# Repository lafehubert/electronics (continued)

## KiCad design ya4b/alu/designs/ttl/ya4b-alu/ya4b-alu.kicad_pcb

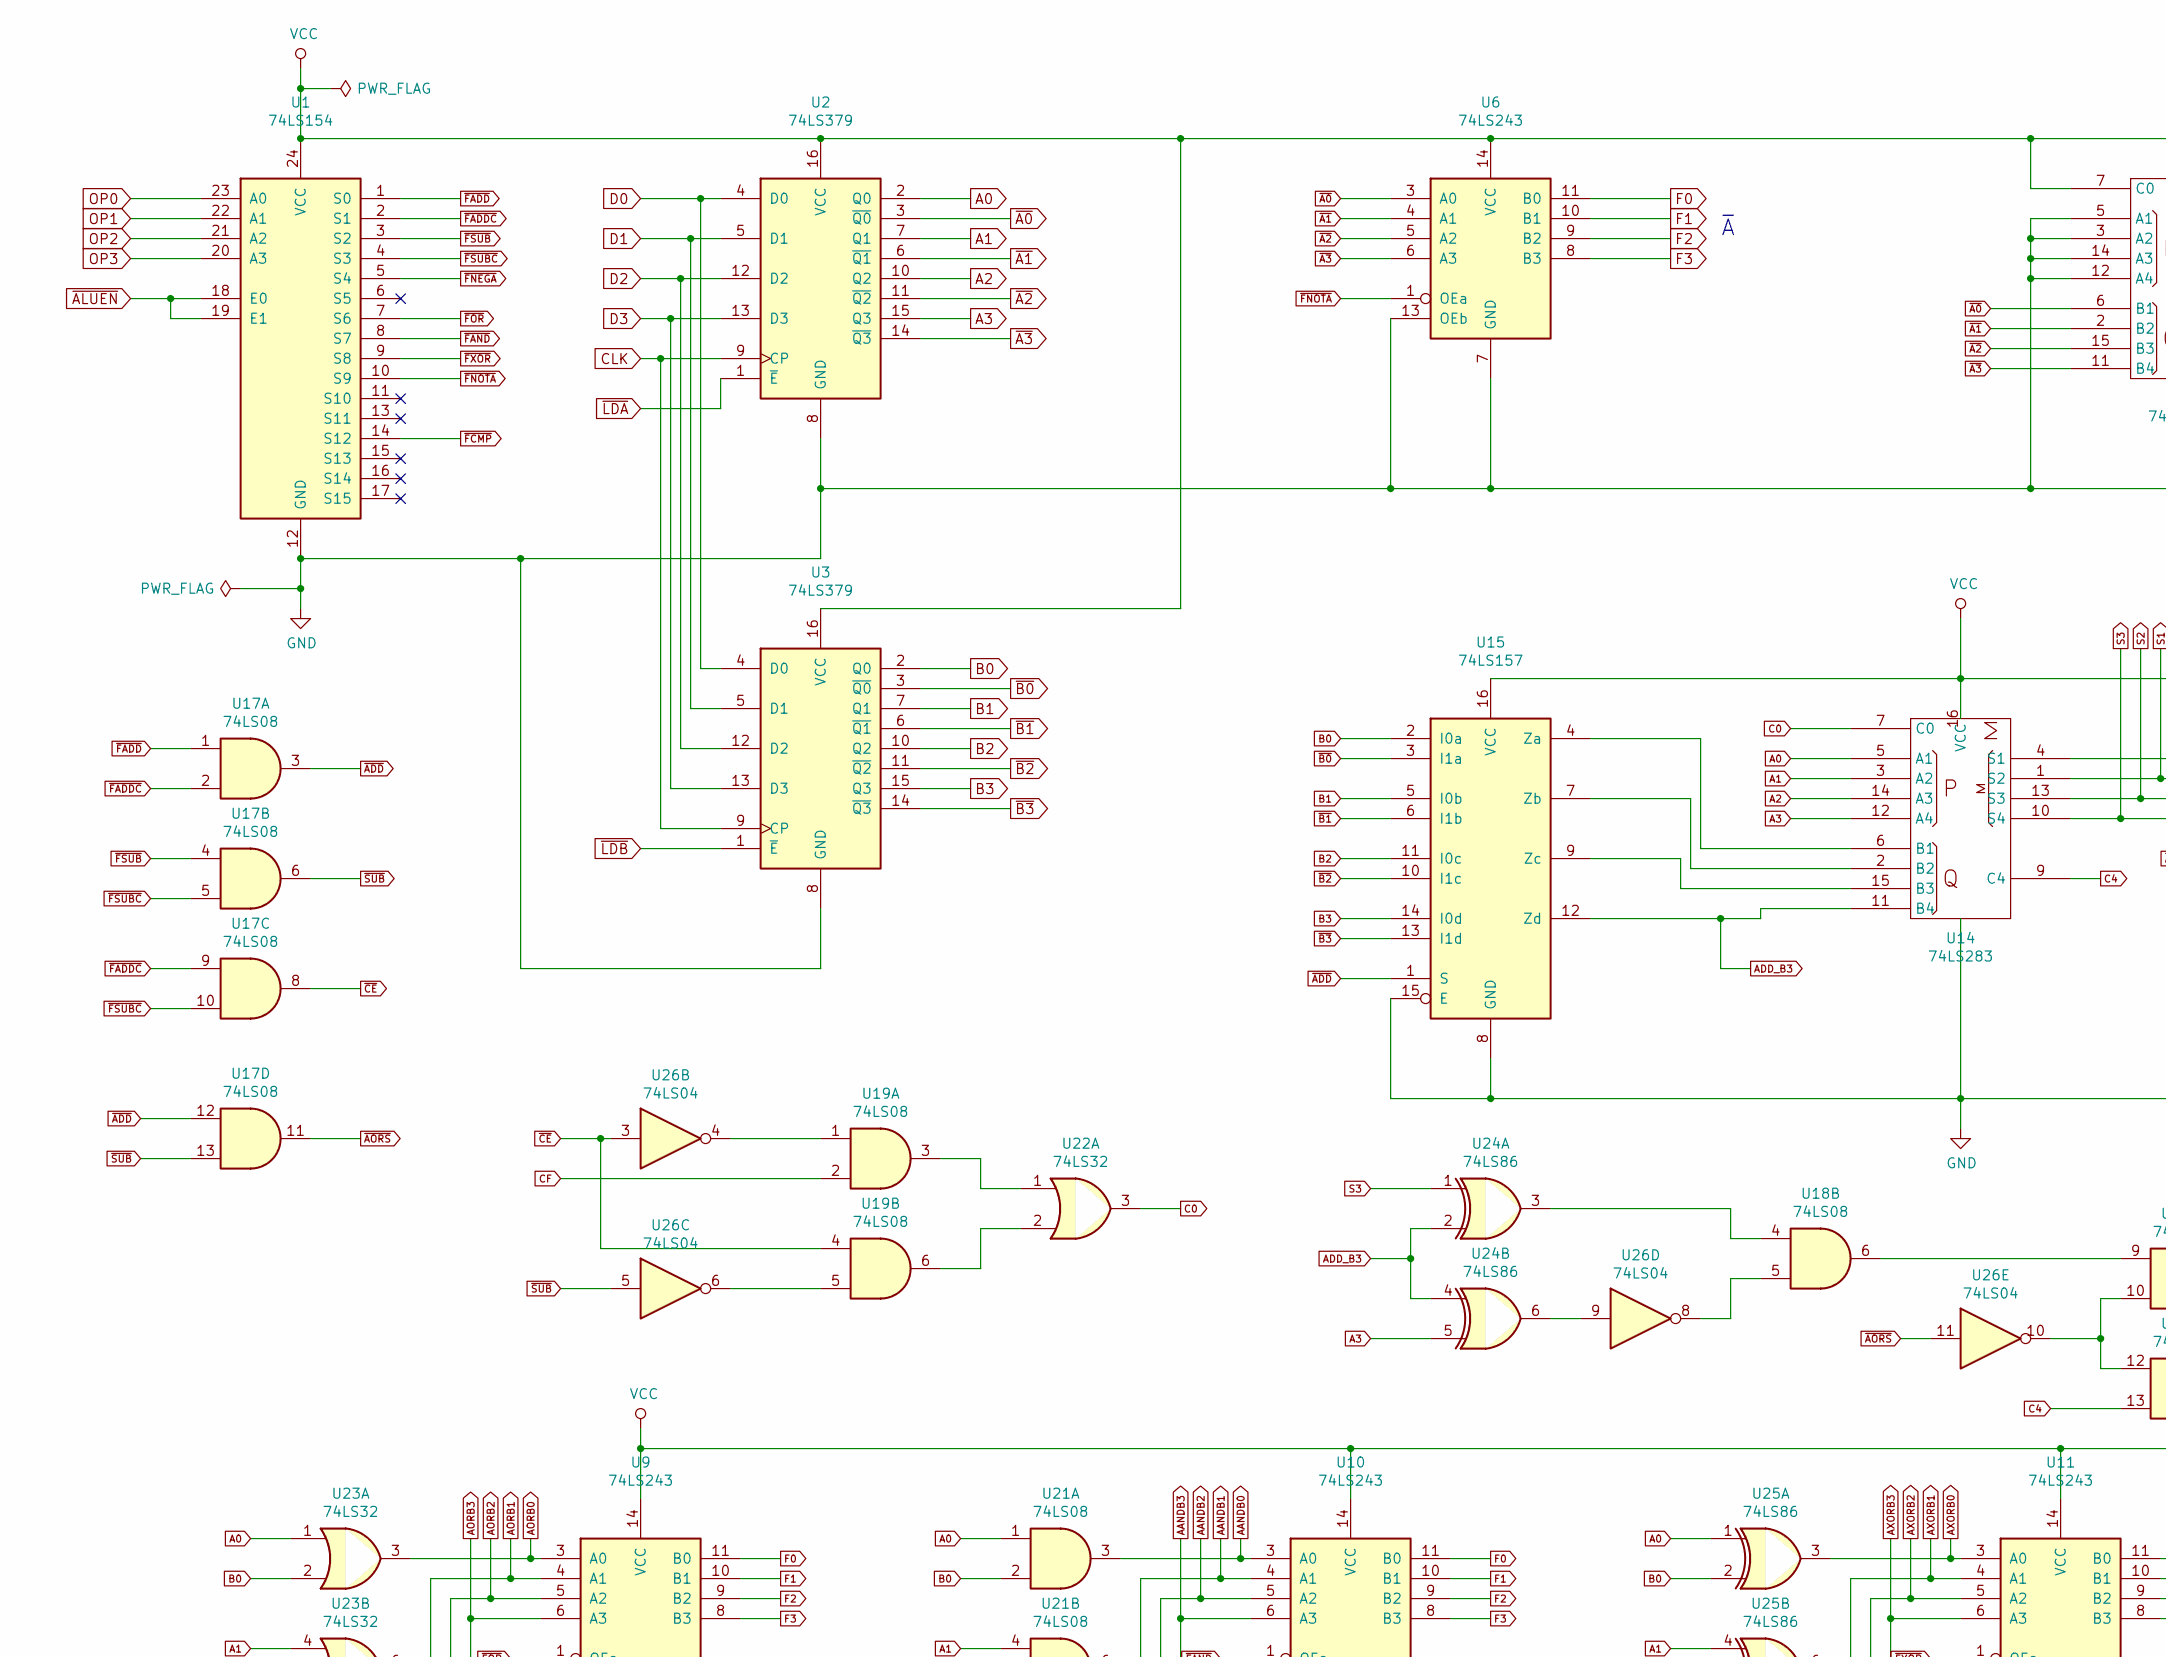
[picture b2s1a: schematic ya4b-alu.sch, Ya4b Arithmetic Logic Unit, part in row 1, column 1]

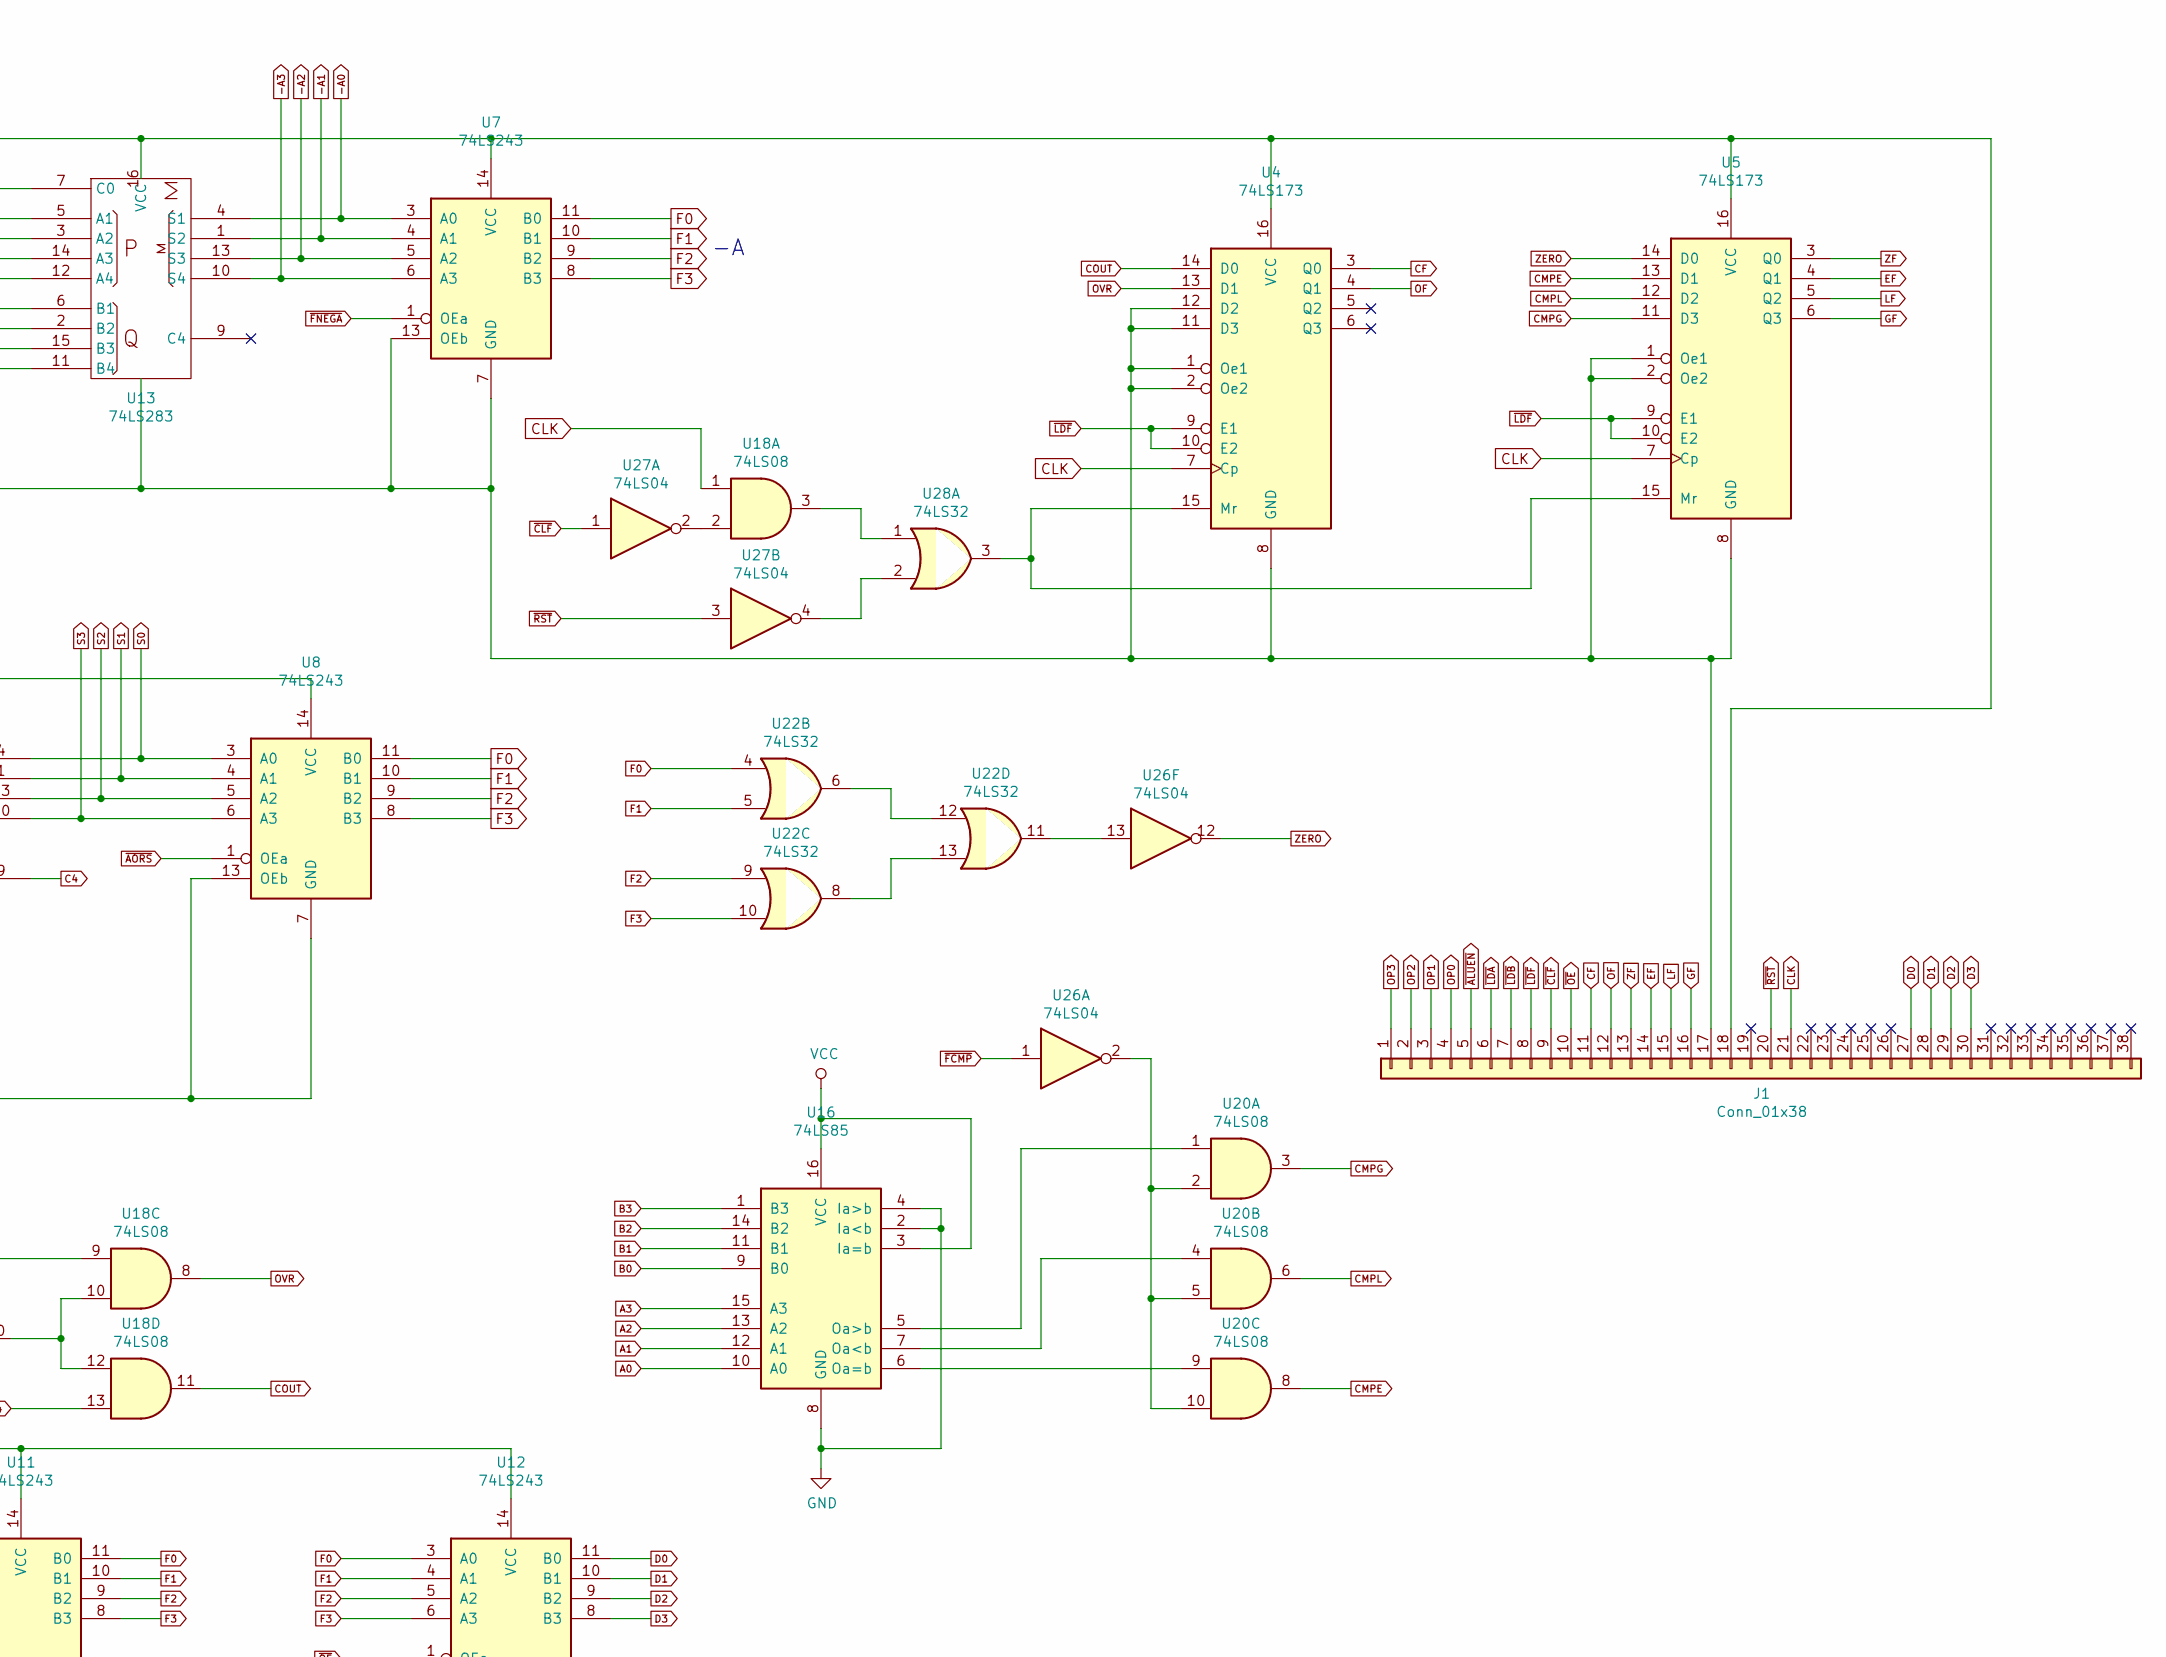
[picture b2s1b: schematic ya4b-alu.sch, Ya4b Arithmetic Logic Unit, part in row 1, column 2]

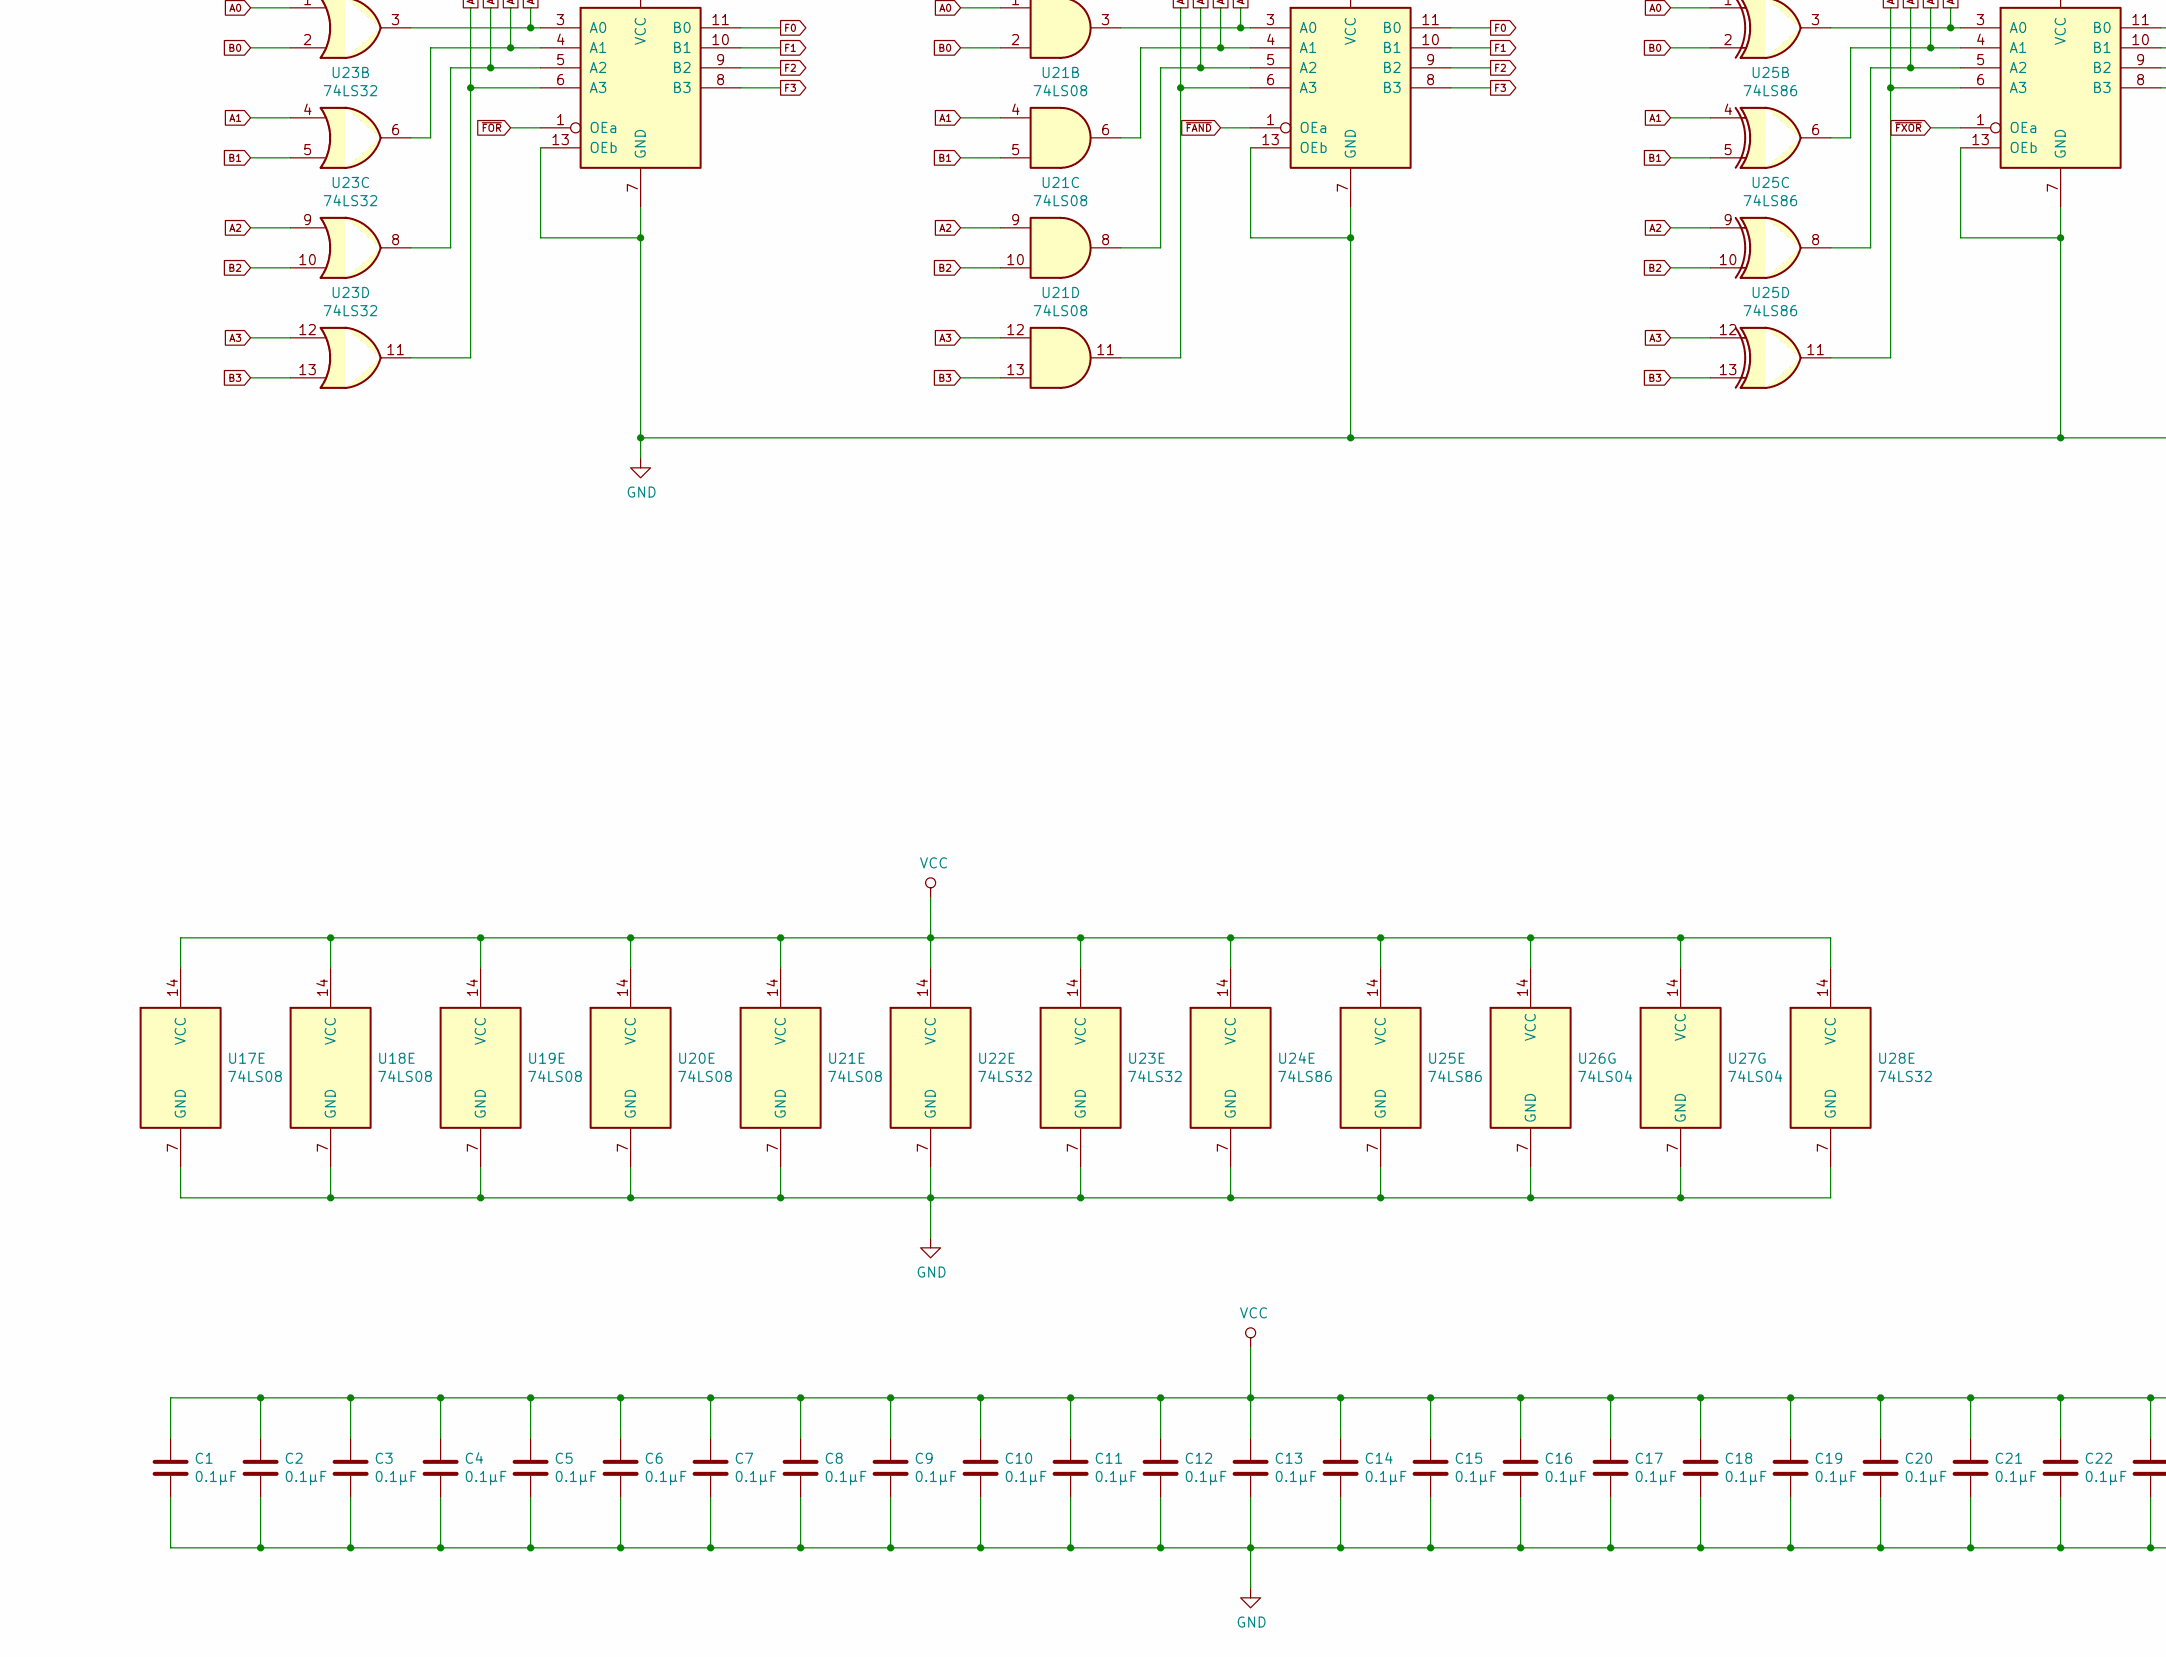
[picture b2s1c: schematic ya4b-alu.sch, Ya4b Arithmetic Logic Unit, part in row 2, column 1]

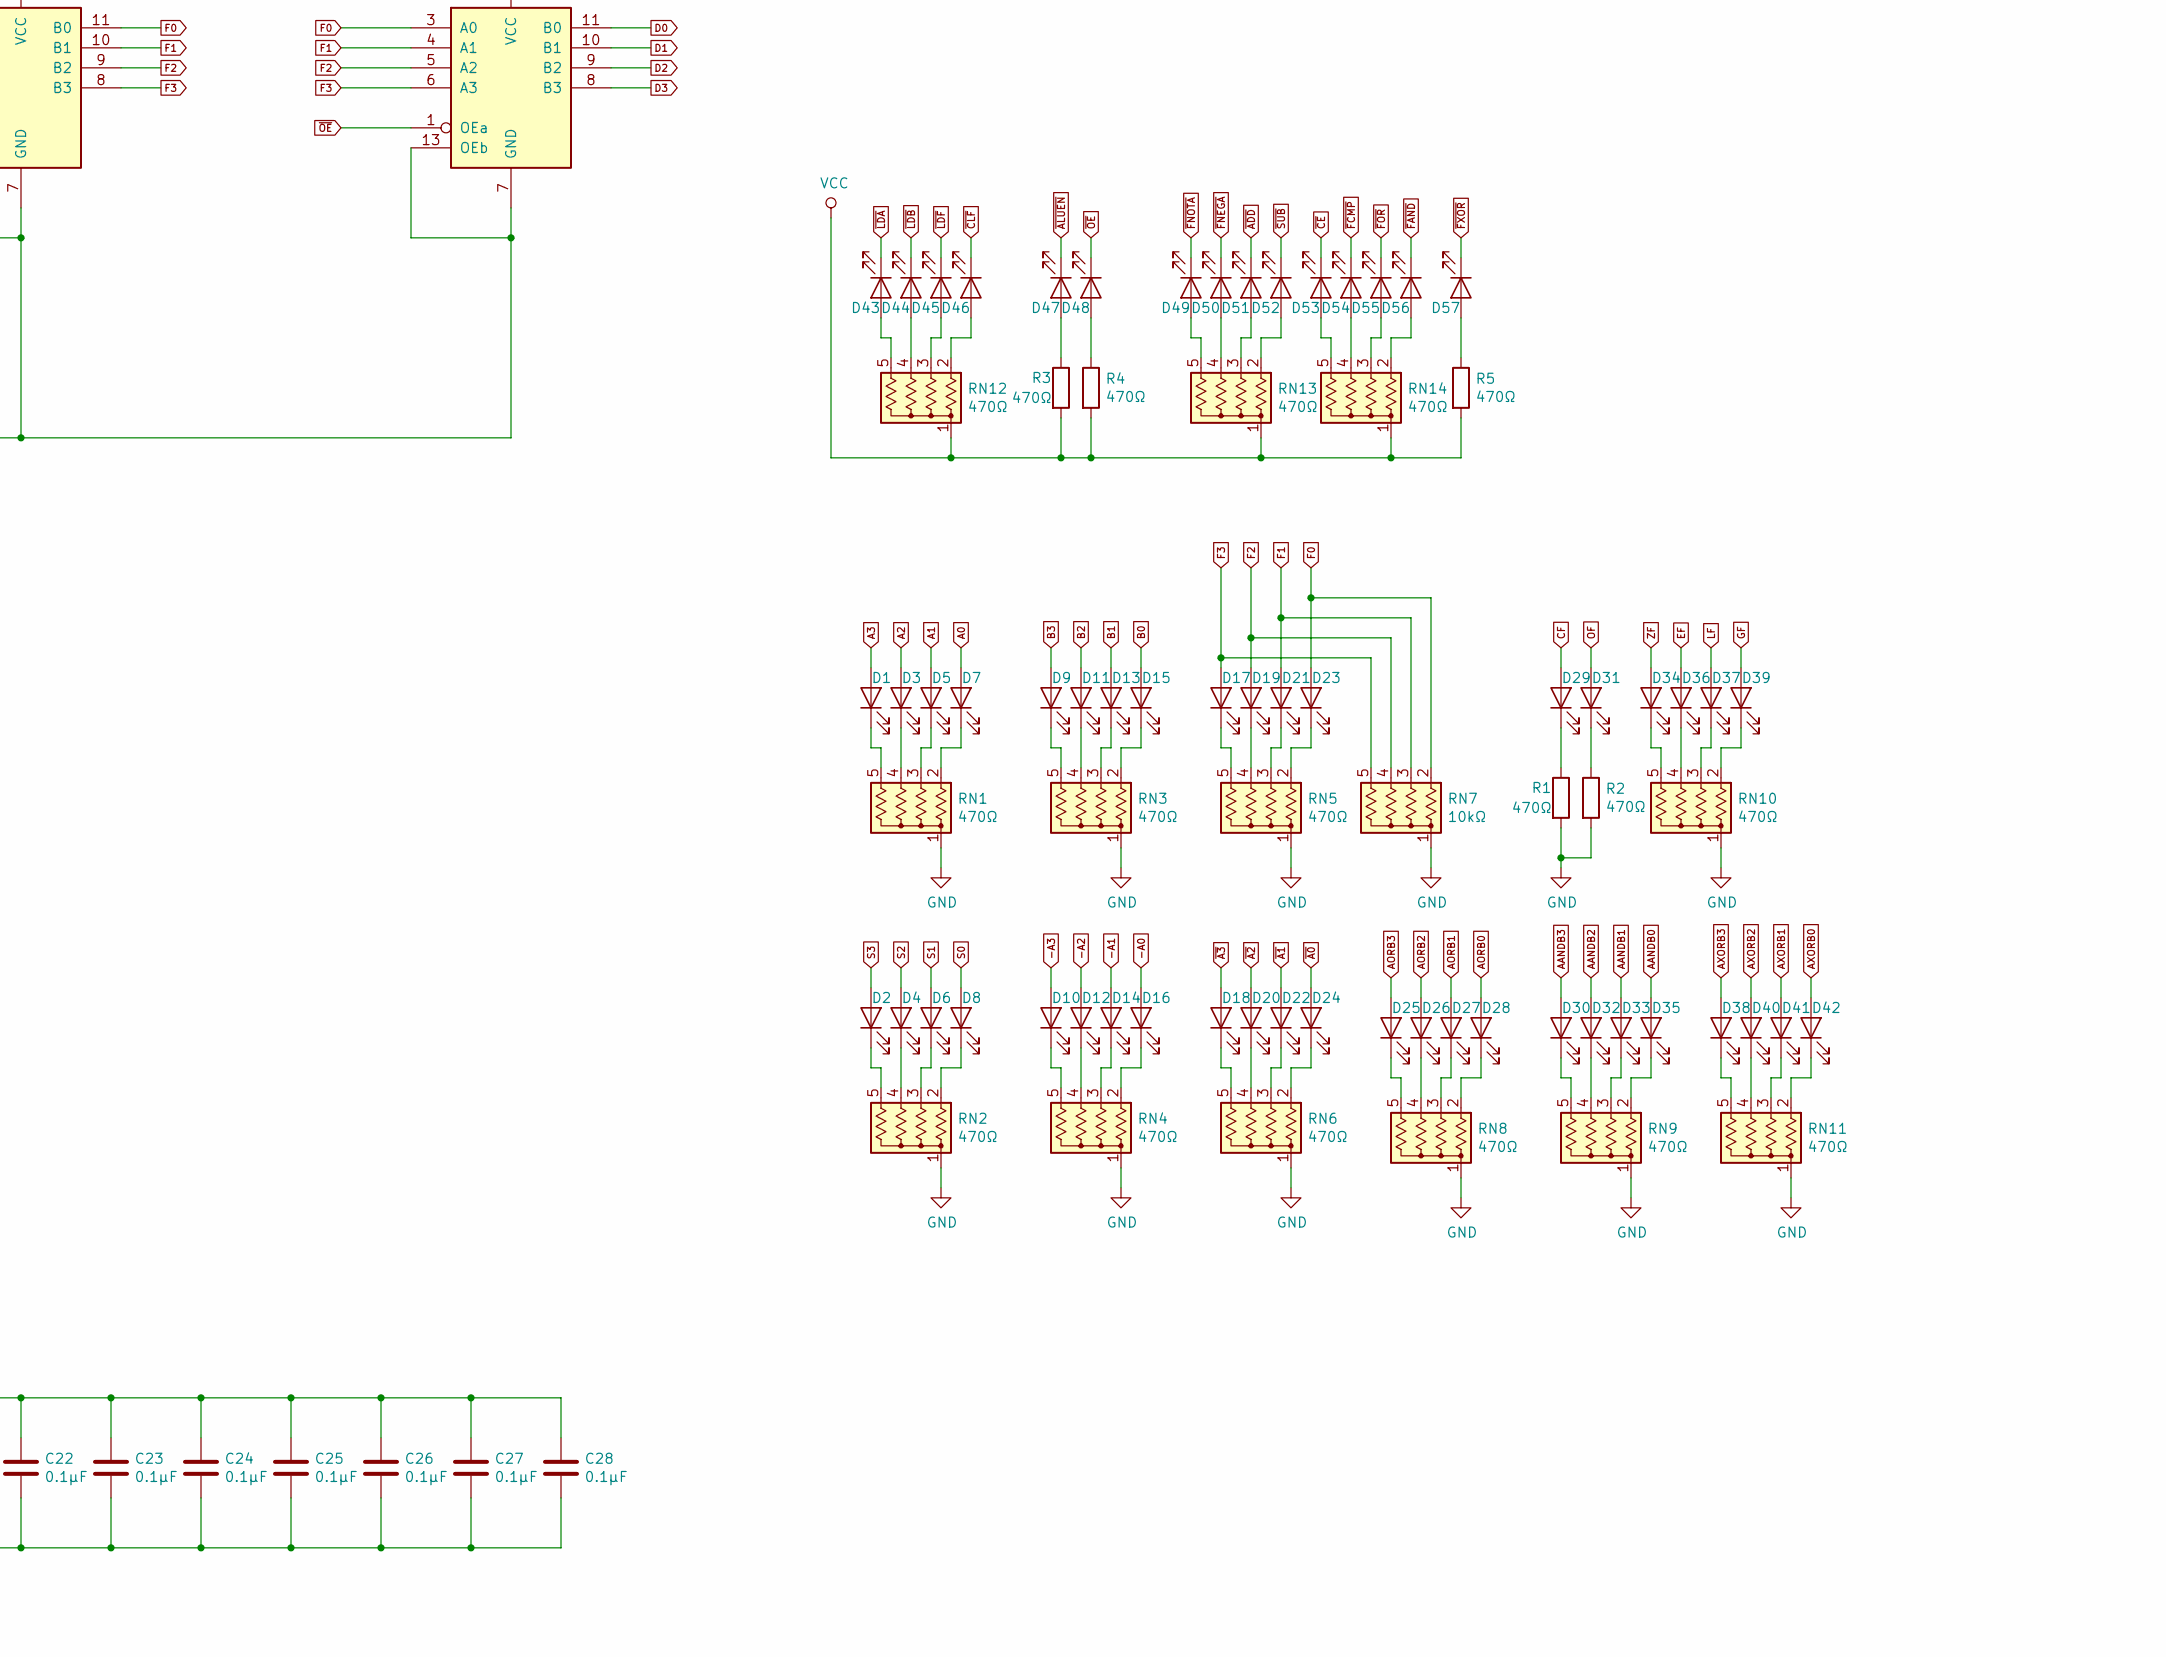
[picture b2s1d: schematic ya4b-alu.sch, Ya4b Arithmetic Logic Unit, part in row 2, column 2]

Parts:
C1, C2, C3, C4, C5, C6, C7, C8, C9, C10, C11, C12, C13, C14, C15, C16, C17, C18, C19, C20, C21, C22, C23, C24, C25, C26, C27, C28: 0.1µF; C_Disc_D3.0mm_W1.6mm_P2.50mm
D1, D2, D3, D4, D5, D6, D7, D8, D9, D10, D11, D12, D13, D14, D15, D16, D17, D18, D19, D20, D21, D22, D23, D24, D25, D26, D27, D28, D29, D30, D31, D32, D33, D34, D35, D36, D37, D38, D39, D40, D41, D42, D43, D44, D45, D46, D47, D48, D49, D50, D51, D52, D53, D54, D55, D56, D57: LED; LED_Rectangular_W5.0mm_H2.0mm
J1: Conn_01x38; PinHeader_1x38_P2.54mm_Vertical
R1, R2, R3, R4, R5: 470Ω; R_Axial_DIN0207_L6.3mm_D2.5mm_P10.16mm_Horizontal
RN1, RN2, RN3, RN4, RN5, RN6, RN8, RN9, RN10, RN11, RN12, RN13, RN14: 470Ω; R_Array_SIP5
RN7: 10kΩ; R_Array_SIP5
U1: 74LS154; DIP-24_W15.24mm_Socket
U2, U3: 74LS379; DIP-16_W7.62mm_Socket
U4, U5: 74LS173; DIP-16_W7.62mm_Socket
U6, U7, U8, U9, U10, U11, U12: 74LS243; DIP-14_W7.62mm_Socket
U13, U14: 74LS283; DIP-16_W7.62mm_Socket
U15: 74LS157; DIP-16_W7.62mm_Socket
U16: 74LS85; DIP-16_W7.62mm_Socket
U17, U18, U19, U20, U21: 74LS08; DIP-14_W7.62mm_Socket
U22, U23, U28: 74LS32; DIP-14_W7.62mm_Socket
U24, U25: 74LS86; DIP-14_W7.62mm_Socket
U26, U27: 74LS04; DIP-14_W7.62mm_Socket

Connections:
-A0: D16.2 (A), U7.3 (A0), U13.4 (S1)
-A1: D14.2 (A), U7.4 (A1), U13.1 (S2)
-A2: D12.2 (A), U7.5 (A2), U13.13 (S3)
-A3: D10.2 (A), U7.6 (A3), U13.10 (S4)
A0: D7.2 (A), U2.2 (Q0), U14.5 (A1), U16.10 (A0), U21.1, U23.1, U25.1
A1: D5.2 (A), U2.7 (Q1), U14.3 (A2), U16.12 (A1), U21.4, U23.4, U25.4
A2: D3.2 (A), U2.10 (Q2), U14.14 (A3), U16.13 (A2), U21.9, U23.9, U25.9
A3: D1.2 (A), U2.15 (Q3), U14.12 (A4), U16.15 (A3), U21.12, U23.12, U24.5, U25.12
AANDB0: D35.2 (A), U10.3 (A0), U21.3
AANDB1: D33.2 (A), U10.4 (A1), U21.6
AANDB2: D32.2 (A), U10.5 (A2), U21.8
AANDB3: D30.2 (A), U10.6 (A3), U21.11
ADD_B3: U14.11 (B4), U15.12 (Zd), U24.2, U24.4
AORB0: D28.2 (A), U9.3 (A0), U23.3
AORB1: D27.2 (A), U9.4 (A1), U23.6
AORB2: D26.2 (A), U9.5 (A2), U23.8
AORB3: D25.2 (A), U9.6 (A3), U23.11
AXORB0: D42.2 (A), U11.3 (A0), U25.3
AXORB1: D41.2 (A), U11.4 (A1), U25.6
AXORB2: D40.2 (A), U11.5 (A2), U25.8
AXORB3: D38.2 (A), U11.6 (A3), U25.11
B0: D15.2 (A), U3.2 (Q0), U15.2 (I0a), U16.9 (B0), U21.2, U23.2, U25.2
B1: D13.2 (A), U3.7 (Q1), U15.5 (I0b), U16.11 (B1), U21.5, U23.5, U25.5
B2: D11.2 (A), U3.10 (Q2), U15.11 (I0c), U16.14 (B2), U21.10, U23.10, U25.10
B3: D9.2 (A), U3.15 (Q3), U15.14 (I0d), U16.1 (B3), U21.13, U23.13, U25.13
C0: U14.7 (C0), U22.3
C4: U14.9 (C4), U18.13
CF: D29.2 (A), J1.11, U4.3 (Q0), U19.2
CLK: J1.21, U2.9 (CP), U3.9 (CP), U4.7 (Cp), U5.7 (Cp), U18.1
CMPE: U5.13 (D1), U20.8
CMPG: U5.11 (D3), U20.3
CMPL: U5.12 (D2), U20.6
COUT: U4.14 (D0), U18.11
D0: J1.27, U2.4 (D0), U3.4 (D0), U12.11 (B0)
D1: J1.28, U2.5 (D1), U3.5 (D1), U12.10 (B1)
D2: J1.29, U2.12 (D2), U3.12 (D2), U12.9 (B2)
D3: J1.30, U2.13 (D3), U3.13 (D3), U12.8 (B3)
EF: D36.2 (A), J1.14, U5.4 (Q1)
F0: D23.2 (A), RN7.2 (R1), U6.11 (B0), U7.11 (B0), U8.11 (B0), U9.11 (B0), U10.11 (B0), U11.11 (B0), U12.3 (A0), U22.4
F1: D21.2 (A), RN7.3 (R2), U6.10 (B1), U7.10 (B1), U8.10 (B1), U9.10 (B1), U10.10 (B1), U11.10 (B1), U12.4 (A1), U22.5
F2: D19.2 (A), RN7.4 (R3), U6.9 (B2), U7.9 (B2), U8.9 (B2), U9.9 (B2), U10.9 (B2), U11.9 (B2), U12.5 (A2), U22.9
F3: D17.2 (A), RN7.5 (R4), U6.8 (B3), U7.8 (B3), U8.8 (B3), U9.8 (B3), U10.8 (B3), U11.8 (B3), U12.6 (A3), U22.10
GF: D39.2 (A), J1.16, U5.6 (Q3)
GND: C1.2, C2.2, C3.2, C4.2, C5.2, C6.2, C7.2, C8.2, C9.2, C10.2, C11.2, C12.2, C13.2, C14.2, C15.2, C16.2, C17.2, C18.2, C19.2, C20.2, C21.2, C22.2, C23.2, C24.2, C25.2, C26.2, C27.2, C28.2, J1.17, R1.2, R2.2, RN1.1 (common), RN2.1 (common), RN3.1 (common), RN4.1 (common), RN5.1 (common), RN6.1 (common), RN7.1 (common), RN8.1 (common), RN9.1 (common), RN10.1 (common), RN11.1 (common), U1.12 (GND), U2.8 (GND), U3.8 (GND), U4.1 (Oe1), U4.2 (Oe2), U4.8 (GND), U4.11 (D3), U4.12 (D2), U5.1 (Oe1), U5.2 (Oe2), U5.8 (GND), U6.7 (GND), U6.13 (OEb), U7.7 (GND), U7.13 (OEb), U8.7 (GND), U8.13 (OEb), U9.7 (GND), U9.13 (OEb), U10.7 (GND), U10.13 (OEb), U11.7 (GND), U11.13 (OEb), U12.7 (GND), U12.13 (OEb), U13.3 (A2), U13.5 (A1), U13.8 (GND), U13.12 (A4), U13.14 (A3), U14.8 (GND), U15.8 (GND), U15.15 (E), U16.2 (Ia<b), U16.4 (Ia>b), U16.8 (GND), U17.7 (GND), U18.7 (GND), U19.7 (GND), U20.7 (GND), U21.7 (GND), U22.7 (GND), U23.7 (GND), U24.7 (GND), U25.7 (GND), U26.7 (GND), U27.7 (GND), U28.7 (GND)
LF: D37.2 (A), J1.15, U5.5 (Q2)
unnamed: D1.1 (K), RN1.5 (R4)
unnamed: D2.1 (K), RN2.5 (R4)
unnamed: D3.1 (K), RN1.4 (R3)
unnamed: D4.1 (K), RN2.4 (R3)
unnamed: D5.1 (K), RN1.3 (R2)
unnamed: D6.1 (K), RN2.3 (R2)
unnamed: D7.1 (K), RN1.2 (R1)
unnamed: D8.1 (K), RN2.2 (R1)
unnamed: D9.1 (K), RN3.5 (R4)
unnamed: D10.1 (K), RN4.5 (R4)
unnamed: D11.1 (K), RN3.4 (R3)
unnamed: D12.1 (K), RN4.4 (R3)
unnamed: D13.1 (K), RN3.3 (R2)
unnamed: D14.1 (K), RN4.3 (R2)
unnamed: D15.1 (K), RN3.2 (R1)
unnamed: D16.1 (K), RN4.2 (R1)
unnamed: D17.1 (K), RN5.5 (R4)
unnamed: D18.1 (K), RN6.5 (R4)
unnamed: D19.1 (K), RN5.4 (R3)
unnamed: D20.1 (K), RN6.4 (R3)
unnamed: D21.1 (K), RN5.3 (R2)
unnamed: D22.1 (K), RN6.3 (R2)
unnamed: D23.1 (K), RN5.2 (R1)
unnamed: D24.1 (K), RN6.2 (R1)
unnamed: D25.1 (K), RN8.5 (R4)
unnamed: D26.1 (K), RN8.4 (R3)
unnamed: D27.1 (K), RN8.3 (R2)
unnamed: D28.1 (K), RN8.2 (R1)
unnamed: D29.1 (K), R1.1
unnamed: D30.1 (K), RN9.5 (R4)
unnamed: D31.1 (K), R2.1
unnamed: D32.1 (K), RN9.4 (R3)
unnamed: D33.1 (K), RN9.3 (R2)
unnamed: D34.1 (K), RN10.5 (R4)
unnamed: D35.1 (K), RN9.2 (R1)
unnamed: D36.1 (K), RN10.4 (R3)
unnamed: D37.1 (K), RN10.3 (R2)
unnamed: D38.1 (K), RN11.5 (R4)
unnamed: D39.1 (K), RN10.2 (R1)
unnamed: D40.1 (K), RN11.4 (R3)
unnamed: D41.1 (K), RN11.3 (R2)
unnamed: D42.1 (K), RN11.2 (R1)
unnamed: D43.2 (A), RN12.5 (R4)
unnamed: D44.2 (A), RN12.4 (R3)
unnamed: D45.2 (A), RN12.3 (R2)
unnamed: D46.2 (A), RN12.2 (R1)
unnamed: D47.2 (A), R3.1
unnamed: D48.2 (A), R4.1
unnamed: D49.2 (A), RN13.5 (R4)
unnamed: D50.2 (A), RN13.4 (R3)
unnamed: D51.2 (A), RN13.3 (R2)
unnamed: D52.2 (A), RN13.2 (R1)
unnamed: D53.2 (A), RN14.5 (R4)
unnamed: D54.2 (A), RN14.4 (R3)
unnamed: D55.2 (A), RN14.3 (R2)
unnamed: D56.2 (A), RN14.2 (R1)
unnamed: D57.2 (A), R5.1
unnamed: U14.2 (B2), U15.7 (Zb)
unnamed: U14.6 (B1), U15.4 (Za)
unnamed: U14.15 (B3), U15.9 (Zc)
unnamed: U16.5 (Oa>b), U20.1
unnamed: U16.6 (Oa=b), U20.9
unnamed: U16.7 (Oa<b), U20.4
unnamed: U18.2, U27.2
unnamed: U18.3, U28.1
unnamed: U18.4, U24.3
unnamed: U18.5, U26.8
unnamed: U18.6, U18.9
unnamed: U18.10, U18.12, U26.10
unnamed: U19.1, U26.4
unnamed: U19.3, U22.1
unnamed: U19.5, U26.6
unnamed: U19.6, U22.2
unnamed: U20.2, U20.5, U20.10, U26.2
unnamed: U22.11, U26.13
unnamed: U22.6, U22.12
unnamed: U22.8, U22.13
unnamed: U24.6, U26.9
unnamed: U27.4, U28.2
unnamed: U4.15 (Mr), U5.15 (Mr), U28.3
OF: D31.2 (A), J1.12, U4.4 (Q1)
OP0: J1.4, U1.23 (A0)
OP1: J1.3, U1.22 (A1)
OP2: J1.2, U1.21 (A2)
OP3: J1.1, U1.20 (A3)
OVR: U4.13 (D1), U18.8
S0: D8.2 (A), U8.3 (A0), U14.4 (S1)
S1: D6.2 (A), U8.4 (A1), U14.1 (S2)
S2: D4.2 (A), U8.5 (A2), U14.13 (S3)
S3: D2.2 (A), U8.6 (A3), U14.10 (S4), U24.1
VCC: C1.1, C2.1, C3.1, C4.1, C5.1, C6.1, C7.1, C8.1, C9.1, C10.1, C11.1, C12.1, C13.1, C14.1, C15.1, C16.1, C17.1, C18.1, C19.1, C20.1, C21.1, C22.1, C23.1, C24.1, C25.1, C26.1, C27.1, C28.1, J1.18, R3.2, R4.2, R5.2, RN12.1 (common), RN13.1 (common), RN14.1 (common), U1.24 (VCC), U2.16 (VCC), U3.16 (VCC), U4.16 (VCC), U5.16 (VCC), U6.14 (VCC), U7.14 (VCC), U8.14 (VCC), U9.14 (VCC), U10.14 (VCC), U11.14 (VCC), U12.14 (VCC), U13.7 (C0), U13.16 (VCC), U14.16 (VCC), U15.16 (VCC), U16.3 (Ia=b), U16.16 (VCC), U17.14 (VCC), U18.14 (VCC), U19.14 (VCC), U20.14 (VCC), U21.14 (VCC), U22.14 (VCC), U23.14 (VCC), U24.14 (VCC), U25.14 (VCC), U26.14 (VCC), U27.14 (VCC), U28.14 (VCC)
ZERO: U5.14 (D0), U26.12
ZF: D34.2 (A), J1.13, U5.3 (Q0)
~A0: D24.2 (A), U2.3 (~Q0), U6.3 (A0), U13.6 (B1)
~A1: D22.2 (A), U2.6 (~Q1), U6.4 (A1), U13.2 (B2)
~A2: D20.2 (A), U2.11 (~Q2), U6.5 (A2), U13.15 (B3)
~A3: D18.2 (A), U2.14 (~Q3), U6.6 (A3), U13.11 (B4)
~ADD: D51.1 (K), U15.1 (S), U17.3, U17.12
~ALUEN: D47.1 (K), J1.5, U1.18 (E0), U1.19 (E1)
~AORS: U8.1 (OEa), U17.11, U26.11
~B0: U3.3 (~Q0), U15.3 (I1a)
~B1: U3.6 (~Q1), U15.6 (I1b)
~B2: U3.11 (~Q2), U15.10 (I1c)
~B3: U3.14 (~Q3), U15.13 (I1d)
~CE: D53.1 (K), U17.8, U19.4, U26.3
~CLF: D46.1 (K), J1.9, U27.1
~FADD: U1.1 (S0), U17.1
~FADDC: U1.2 (S1), U17.2, U17.9
~FAND: D56.1 (K), U1.8 (S7), U10.1 (OEa)
~FCMP: D54.1 (K), U1.14 (S12), U26.1
~FNEGA: D50.1 (K), U1.5 (S4), U7.1 (OEa)
~FNOTA: D49.1 (K), U1.10 (S9), U6.1 (OEa)
~FOR: D55.1 (K), U1.7 (S6), U9.1 (OEa)
~FSUB: U1.3 (S2), U17.4
~FSUBC: U1.4 (S3), U17.5, U17.10
~FXOR: D57.1 (K), U1.9 (S8), U11.1 (OEa)
~LDA: D43.1 (K), J1.6, U2.1 (~E)
~LDB: D44.1 (K), J1.7, U3.1 (~E)
~LDF: D45.1 (K), J1.8, U4.9 (E1), U4.10 (E2), U5.9 (E1), U5.10 (E2)
~OE: D48.1 (K), J1.10, U12.1 (OEa)
~RST: J1.20, U27.3
~SUB: D52.1 (K), U17.6, U17.13, U26.5

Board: 2 copper layers, 133 parts (0 on the bottom side), 167 nets, no tracks yet.
